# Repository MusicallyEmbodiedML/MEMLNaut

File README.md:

Hardware for the MEMLNaut instrument

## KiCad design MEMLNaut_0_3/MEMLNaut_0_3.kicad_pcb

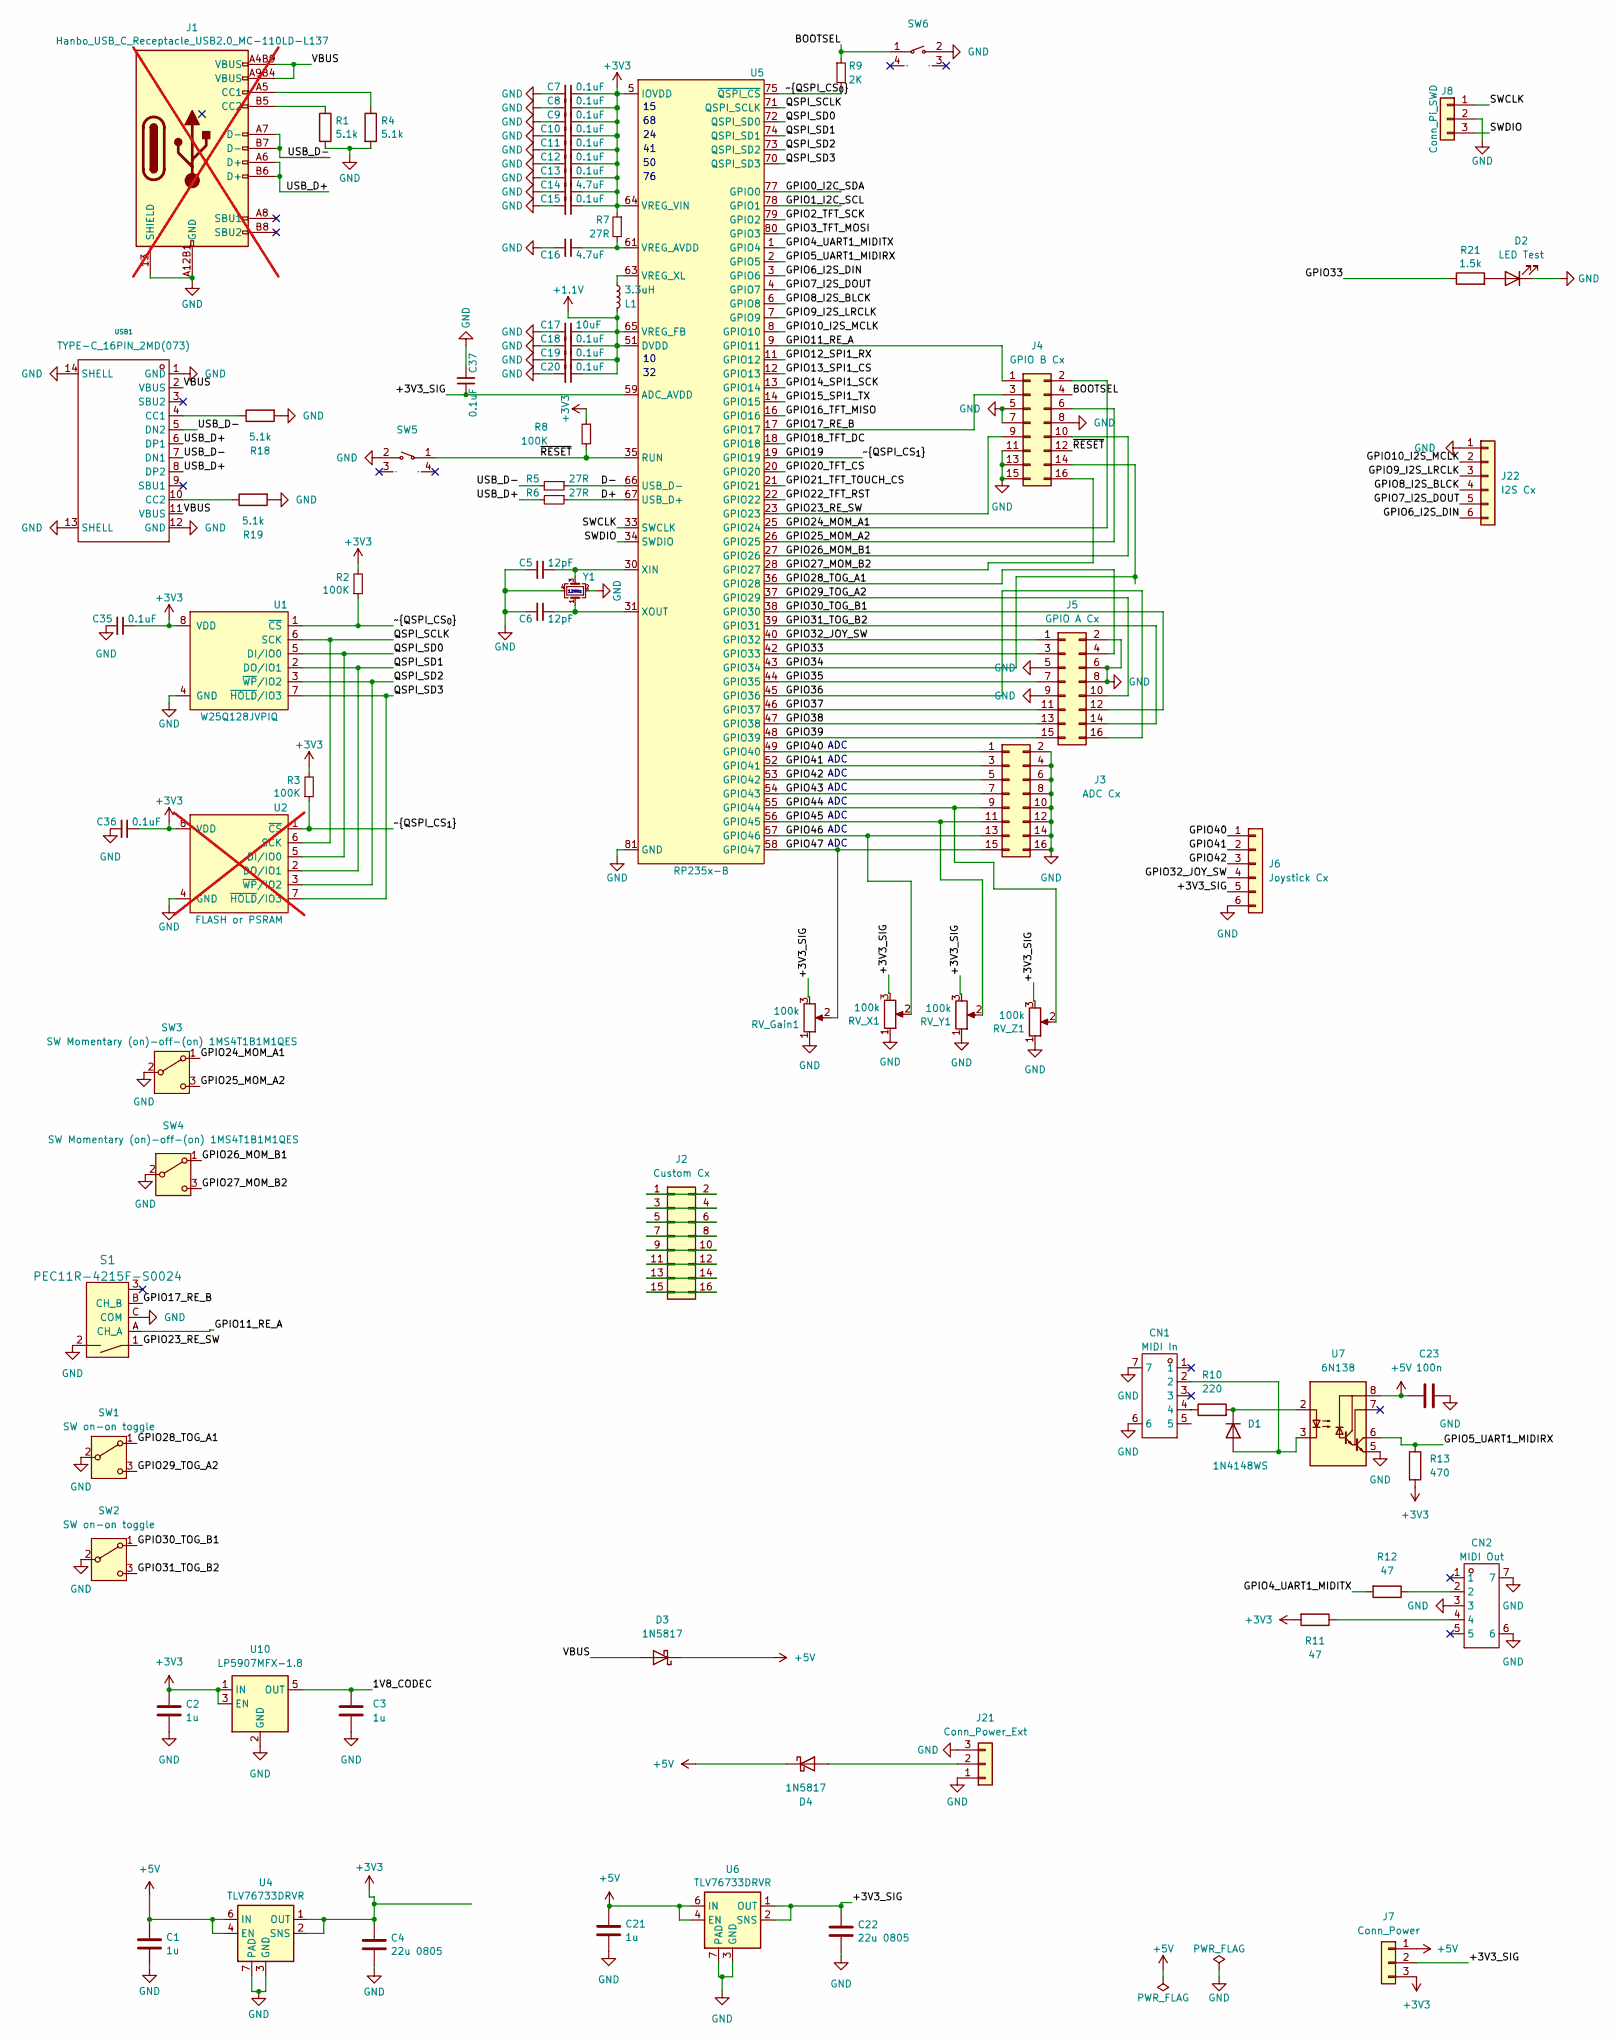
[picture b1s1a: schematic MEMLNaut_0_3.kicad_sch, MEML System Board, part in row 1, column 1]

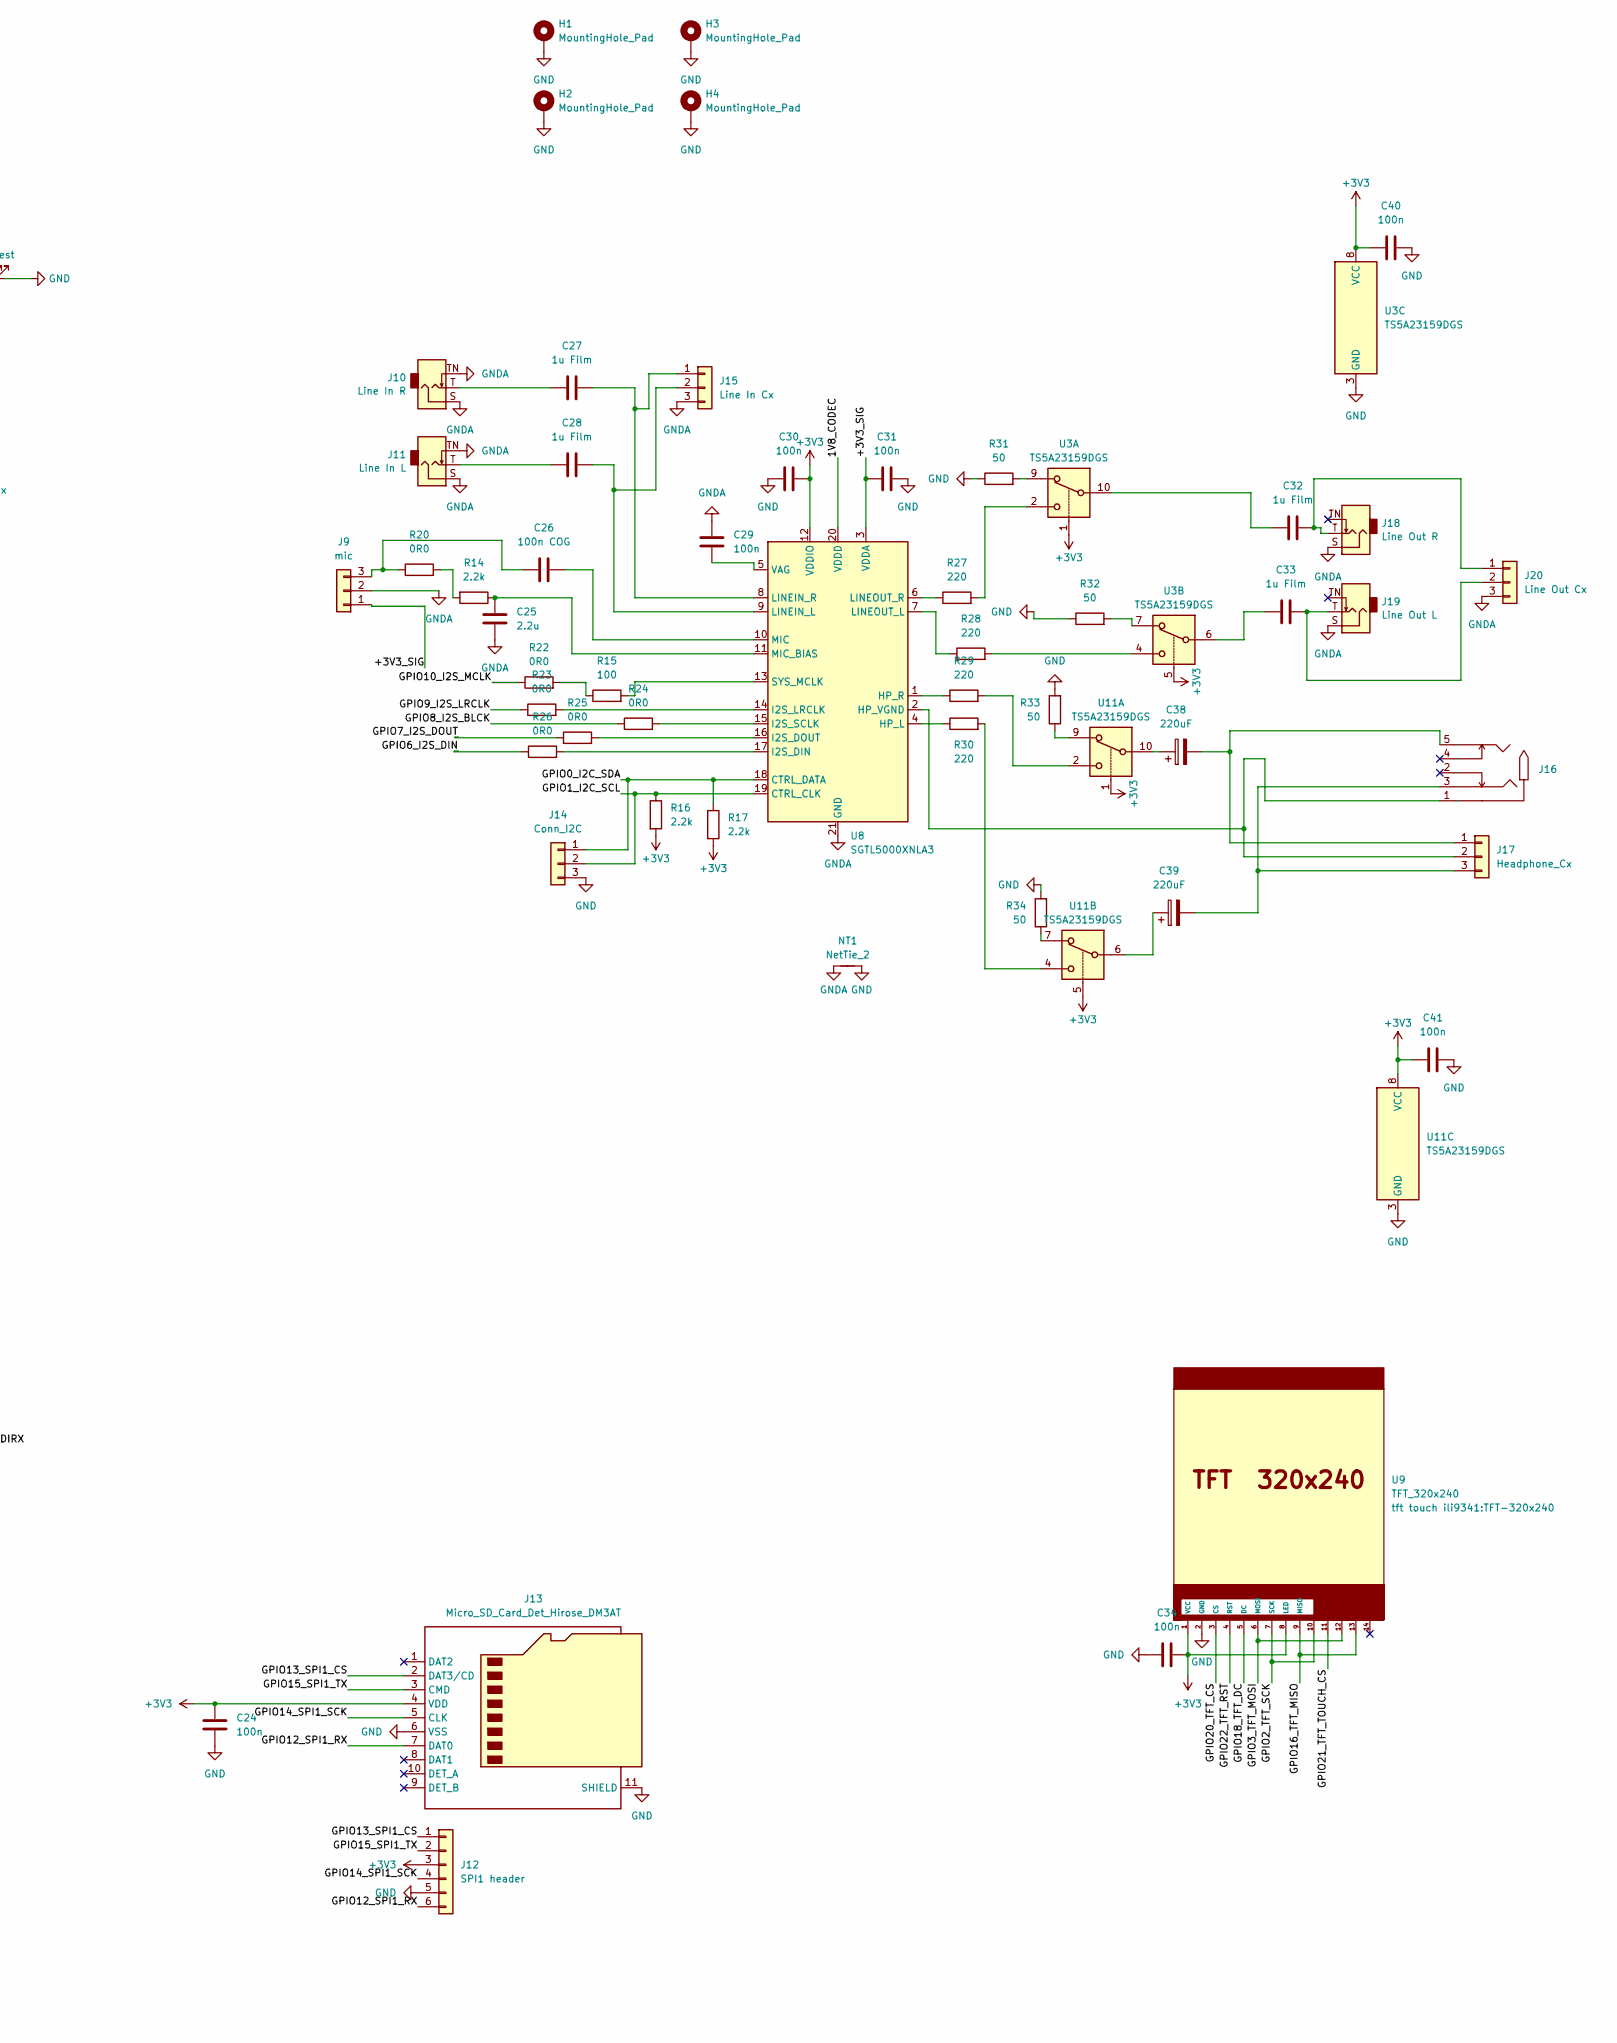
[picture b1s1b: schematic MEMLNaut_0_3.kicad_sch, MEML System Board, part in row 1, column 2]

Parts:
C1, C2, C21: 1u; C_0603_1608Metric_Pad1.08x0.95mm_HandSolder
C3: 1u; C_0603_1608Metric
C4, C22: 22u 0805; C_0805_2012Metric_Pad1.18x1.45mm_HandSolder
C5, C6: 12pF; C_0603_1608Metric
C7, C8, C9, C10, C11, C12, C13, C15, C18, C19, C20, C35, C36, C37: 0.1uF; C_0603_1608Metric
C14, C16: 4.7uF; C_0603_1608Metric
C17: 10uF; C_0603_1608Metric
C23, C24, C29, C30, C31, C34, C40, C41: 100n; C_0603_1608Metric
C25: 2.2u; C_0603_1608Metric
C26: 100n COG; C_Rect_L13.0mm_W5.0mm_P10.00mm_FKS3_FKP3_MKS4; JLC C109501
C27, C28, C32, C33: 1u Film; C_Rect_L13.0mm_W6.0mm_P10.00mm_FKS3_FKP3_MKS4; JLC C2928853
C38, C39: 220uF; CP_Elec_8x10; JLC C445468
CN1: MIDI In; CONN-TH_DIN-504B-M10; Manufacturer Part DIN-504B-M10; LCSC Part Name DIN-504B-M10
CN2: MIDI Out; CONN-TH_DIN-504B-M10; Manufacturer Part DIN-504B-M10; LCSC Part Name DIN-504B-M10
D1: 1N4148WS; D_SOD-323
D2: LED Test; LED_0805_2012Metric
D3, D4: 1N5817; D_SOD-323
H1, H2, H3, H4: MountingHole_Pad; MountingHole_2.2mm_M2_DIN965_Pad
J1: Hanbo_USB_C_Receptacle_USB2.0_MC-110LD-L137; USB-C-TH_MC-110LD-L137-A; not fitted
J2: Custom Cx; HDR-SMD_16P-P2.54-V-M-R2-C8-S7.4; JLC C3294466
J3: ADC Cx; HDR-SMD_16P-P2.54-V-M-R2-C8-S7.4; JLC C3294466
J4: GPIO B Cx; HDR-SMD_16P-P2.54-V-M-R2-C8-S7.4; JLC C3294466
J5: GPIO A Cx; HDR-SMD_16P-P2.54-V-M-R2-C8-S7.4; JLC C3294466
J6: Joystick Cx; HDR-SMD_6P-P2.54-V-M-S4.8; JLC C5160789
J7: Conn_Power; HDR-TH_3P-P2.54_DZ254S-11-03-48; JLC C5160786
J8: Conn_Pi_SWD; HDR-TH_3P-P2.54_DZ254S-11-03-48; JLC C5160786
J9: mic; HDR-TH_3P-P2.54_DZ254S-11-03-48; JLC C5160786
J10: Line In R; Jack_3.5mm_QingPu_WQP-PJ398SM_Vertical_CircularHoles
J11: Line In L; Jack_3.5mm_QingPu_WQP-PJ398SM_Vertical_CircularHoles
J12: SPI1 header; PinHeader_1x06_P2.54mm_Vertical; JLC C5160789
J13: Micro_SD_Card_Det_Hirose_DM3AT; microSD_HC_Hirose_DM3AT-SF-PEJM5; JLC C114218
J14: Conn_I2C; HDR-TH_3P-P2.54_DZ254S-11-03-48; JLC C5160786
J15: Line In Cx; HDR-TH_3P-P2.54_DZ254S-11-03-48; JLC C5160786
J16: AUDIO-TH_PJ-325C; Manufacturer Part PJ325外铜套; LCSC Part Name 3.5mm耳机座
J17: Headphone_Cx; HDR-TH_3P-P2.54_DZ254S-11-03-48; JLC C5160786
J18: Line Out R; Jack_3.5mm_QingPu_WQP-PJ398SM_Vertical_CircularHoles
J19: Line Out L; Jack_3.5mm_QingPu_WQP-PJ398SM_Vertical_CircularHoles
J20: Line Out Cx; HDR-TH_3P-P2.54_DZ254S-11-03-48; JLC C5160786
J21: Conn_Power_Ext; HDR-TH_3P-P2.54_DZ254S-11-03-48; JLC C5160786
J22: I2S Cx; HDR-SMD_6P-P2.54-V-M-S4.8; JLC C5160789
L1: 3.3uH; IND-SMD_L2.0-W1.6_AOTA-B201610S3R3-101-T; JLC C42411119
NT1: NetTie_2; NetTie-2_SMD_Pad0.5mm
R1, R4, R18, R19: 5.1k; R_0402_1005Metric
R2, R3, R8: 100K; R_0603_1608Metric
R5, R6, R7: 27R; R_0603_1608Metric
R9: 2K; R_0603_1608Metric
R10, R27, R28, R29, R30: 220; R_0603_1608Metric
R11, R12: 47; R_0603_1608Metric
R13: 470; R_0603_1608Metric
R14, R16, R17: 2.2k; R_0603_1608Metric
R15: 100; R_0603_1608Metric
R20, R22, R23, R24, R25, R26: 0R0; R_0603_1608Metric
R21: 1.5k; R_0603_1608Metric
R31, R32, R33, R34: 50; R_0603_1608Metric
RV_Gain1: 100k; Alpha9mmPot
RV_X1: 100k; Alpha9mmPot
RV_Y1: 100k; Alpha9mmPot
RV_Z1: 100k; Alpha9mmPot
S1: PEC11R-4215F-S0024; Rotary_Encoder_Switched_PEC11R; MPN PEC11R-4215F-S0024; Digi-Key_PN PEC11R-4215F-S0024-ND
SW1, SW2: SW on-on toggle; Thonk DWB2
SW3, SW4: SW Momentary (on)-off-(on) 1MS4T1B1M1QES; Thonk DWB2
SW5, SW6: SW-TH_K2-1102AQ-C4CW-01; Manufacturer Part K2-1102AQ-C4CW-01; LCSC Part Name 6*6*5塑头,260G,行程0.25mm,侧脚
U1: W25Q128JVPIQ; WSON-8-1EP_6x5mm_P1.27mm_EP3.4x4mm; LCSC C190862
U2: FLASH or PSRAM; SSOP-8_5.25x5.24mm_P1.27mm; not fitted
U3, U11: TS5A23159DGS; VSSOP-10_3x3mm_P0.5mm
U4, U6: TLV76733DRVR; WSON-6-1EP_2x2mm_P0.65mm_EP1x1.6mm_ThermalVias
U5: RP235x-B; QFN-80_EP_10x10_Pitch0.4mm
U7: 6N138; DIP-8_W7.62mm; JLC C571211
U8: SGTL5000XNLA3; QFN-20-1EP_3x3mm_P0.4mm_EP1.65x1.65mm
U9: TFT_320x240; TFT-320x240
U10: LP5907MFX-1.8; SOT-23-5; JLC C92498
USB1: TYPE-C_16PIN_2MD(073); USB-C-SMD_TYPE-C-6PIN-2MD-073; JLC C2765186
Y1: CM4012M00012001; Crystal_SMD_2520-4Pin_2.5x2.0mm; LCSC C7294611

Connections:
+1.1V: C17.1, C18.1, C19.1, C20.1, L1.2, U5.10 (DVDD), U5.32 (DVDD), U5.51 (DVDD), U5.65 (VREG_FB)
+3V3: C2.1, C4.1, C7.1, C8.1, C9.1, C10.1, C11.1, C12.1, C13.1, C14.1, C15.1, C24.1, C30.2, C34.2, C35.1, C36.1, C40.1, C41.1, J7.3, J12.3, J13.4 (VDD), R2.2, R3.2, R7.1, R8.1, R11.2, R13.2, R16.2, R17.2, U1.8 (VDD), U2.8 (VDD), U3.1, U3.5, U3.8 (VCC), U4.1 (OUT), U4.2 (SNS), U5.5 (IOVDD), U5.15 (IOVDD), U5.24 (IOVDD), U5.29 (IOVDD), U5.41 (IOVDD), U5.50 (IOVDD), U5.60 (IOVDD), U5.64 (VREG_VIN), U5.68 (IOVDD), U5.69 (IOVDD), U5.76 (IOVDD), U8.12 (VDDIO), U9.1 (VCC), U9.8 (LED), U10.1 (IN), U10.3 (EN), U11.1, U11.5, U11.8 (VCC)
+5V: C1.1, C21.1, C23.1, D3.1 (K), D4.1 (K), J7.1, U4.4 (EN), U4.6 (IN), U6.4 (EN), U6.6 (IN), U7.8 (VCC)
/1V8_CODEC: C3.1, U8.20 (VDDD), U10.5 (OUT)
/+3V3_SIG: C22.1, C31.2, C37.1, J6.5, J7.2, J9.1, RV_Gain1.3, RV_X1.3, RV_Y1.3, RV_Z1.3, U5.59 (ADC_AVDD), U6.1 (OUT), U6.2 (SNS), U8.3 (VDDA)
/BOOTSEL: J4.4, R9.1, SW6.1
/D+: R6.1, U5.67 (USB_D+)
/D-: R5.1, U5.66 (USB_D-)
/GPIO0_I2C_SDA: J14.1, R17.1, U5.77 (GPIO0), U8.18 (CTRL_DATA)
/GPIO1_I2C_SCL: J14.2, R16.1, U5.78 (GPIO1), U8.19 (CTRL_CLK)
/GPIO2_TFT_SCK: U5.79 (GPIO2), U9.7 (SCK), U9.10
/GPIO3_TFT_MOSI: U5.80 (GPIO3), U9.6 (MOSI), U9.12
/GPIO4_UART1_MIDITX: R12.2, U5.1 (GPIO4)
/GPIO5_UART1_MIDIRX: R13.1, U5.2 (GPIO5), U7.6 (VO2)
/GPIO6_I2S_DIN: J22.6, R26.1, U5.3 (GPIO6)
/GPIO7_I2S_DOUT: J22.5, R25.1, U5.4 (GPIO7)
/GPIO8_I2S_BLCK: J22.4, R24.1, U5.6 (GPIO8)
/GPIO9_I2S_LRCLK: J22.3, R23.1, U5.7 (GPIO9)
/GPIO10_I2S_MCLK: J22.2, R22.1, U5.8 (GPIO10)
/GPIO11_RE_A: J4.1, S1.A (CH_A), U5.9 (GPIO11)
/GPIO12_SPI1_RX: J12.6, J13.7 (DAT0), U5.11 (GPIO12)
/GPIO13_SPI1_CS: J12.1, J13.2 (DAT3/CD), U5.12 (GPIO13)
/GPIO14_SPI1_SCK: J12.4, J13.5 (CLK), U5.13 (GPIO14)
/GPIO15_SPI1_TX: J12.2, J13.3 (CMD), U5.14 (GPIO15)
/GPIO16_TFT_MISO: U5.16 (GPIO16), U9.9 (MISO), U9.13
/GPIO17_RE_B: J4.3, S1.B (CH_B), U5.17 (GPIO17)
/GPIO18_TFT_DC: U5.18 (GPIO18), U9.5 (DC)
/GPIO19: R3.1, U2.1 (~CS), U5.19 (GPIO19)
/GPIO20_TFT_CS: U5.20 (GPIO20), U9.3 (CS)
/GPIO21_TFT_TOUCH_CS: U5.21 (GPIO21), U9.11
/GPIO22_TFT_RST: U5.22 (GPIO22), U9.4 (RST)
/GPIO23_RE_SW: J4.9, S1.1, U5.23 (GPIO23)
/GPIO24_MOM_A1: J4.2, SW3.1 (A), U5.25 (GPIO24)
/GPIO25_MOM_A2: J4.6, SW3.3 (C), U5.26 (GPIO25)
/GPIO26_MOM_B1: J4.10, SW4.1 (A), U5.27 (GPIO26)
/GPIO27_MOM_B2: J4.16, SW4.3 (C), U5.28 (GPIO27)
/GPIO28_TOG_A1: J5.4, SW1.1 (A), U5.36 (GPIO28)
/GPIO29_TOG_A2: J5.10, SW1.3 (C), U5.37 (GPIO29)
/GPIO30_TOG_B1: J5.12, SW2.1 (A), U5.38 (GPIO30)
/GPIO31_TOG_B2: J5.14, SW2.3 (C), U5.39 (GPIO31)
/GPIO32_JOY_SW: J5.1, J6.4, U5.40 (GPIO32)
/GPIO33: J5.3, R21.1, U5.42 (GPIO33)
/GPIO34: J4.14, U5.43 (GPIO34)
/GPIO35: J5.7, U5.44 (GPIO35)
/GPIO36: J5.16, U5.45 (GPIO36)
/GPIO37: J5.11, U5.46 (GPIO37)
/GPIO38: J5.13, U5.47 (GPIO38)
/GPIO39: J5.15, U5.48 (GPIO39)
/GPIO40: J3.1, J6.1, U5.49 (GPIO40)
/GPIO41: J3.3, J6.2, U5.52 (GPIO41)
/GPIO42: J3.5, J6.3, U5.53 (GPIO42)
/GPIO43: J3.7, U5.54 (GPIO43)
/GPIO44: J3.9, RV_Z1.2, U5.55 (GPIO44)
/GPIO45: J3.11, RV_Y1.2, U5.56 (GPIO45)
/GPIO46: J3.13, RV_X1.2, U5.57 (GPIO46)
/GPIO47: J3.15, RV_Gain1.2, U5.58 (GPIO47)
/QSPI_SCLK: U1.6 (SCK), U2.6 (SCK), U5.71 (QSPI_SCLK)
/QSPI_SD0: U1.5 (DI/IO0), U2.5 (DI/IO0), U5.72 (QSPI_SD0)
/QSPI_SD1: U1.2 (DO/IO1), U2.2 (DO/IO1), U5.74 (QSPI_SD1)
/QSPI_SD2: U1.3 (~WP/IO2), U2.3 (~WP/IO2), U5.73 (QSPI_SD2)
/QSPI_SD3: U1.7 (~HOLD/IO3), U2.7 (~HOLD/IO3), U5.70 (QSPI_SD3)
/SWCLK: J8.1, U5.33 (SWCLK)
/SWDIO: J8.3, U5.34 (SWDIO)
/USB_D+: J1.A6 (D+), J1.B6 (D+), R6.2, USB1.6 (DP1), USB1.8 (DP2)
/USB_D-: J1.A7 (D-), J1.B7 (D-), R5.2, USB1.5 (DN2), USB1.7 (DN1)
/VBUS: D3.2 (A), J1.A4B9 (VBUS), J1.A9B4 (VBUS), USB1.2 (VBUS), USB1.11 (VBUS)
/~QSPI_CS_{0}: R2.1, R9.2, U1.1 (~CS), U5.75 (~QSPI_CS)
/~RESET: J4.12, R8.2, SW5.1, U5.35 (RUN)
GND: C1.2, C2.2, C3.2, C4.2, C5.2, C6.2, C7.2, C8.2, C9.2, C10.2, C11.2, C12.2, C13.2, C14.2, C15.2, C16.2, C17.2, C18.2, C19.2, C20.2, C21.2, C22.2, C23.2, C24.2, C30.1, C31.1, C34.1, C35.2, C36.2, C37.2, C40.2, C41.2, CN1.6, CN1.7, CN2.3, CN2.6, CN2.7, D2.1 (K), H1.1, H2.1, H3.1, H4.1, J1.13 (SHIELD), J1.A1B12 (GND), J1.A12B1 (GND), J3.2, J3.4, J3.6, J3.8, J3.10, J3.12, J3.14, J3.16, J4.5, J4.7, J4.8, J4.11, J4.13, J4.15, J5.2, J5.5, J5.6, J5.8, J5.9, J6.6, J8.2, J12.5, J13.6 (VSS), J13.11 (SHIELD), J14.3, J21.1, J21.3, J22.1, NT1.2, R1.2, R4.2, R18.2, R19.2, R31.1, R32.1, R33.2, R34.2, RV_Gain1.1, RV_X1.1, RV_Y1.1, RV_Z1.1, S1.2, S1.C (COM), SW1.2 (B), SW2.2 (B), SW3.2 (B), SW4.2 (B), SW5.2, SW6.2, U1.4 (GND), U1.9 (GND), U2.4 (GND), U3.3 (GND), U4.3 (GND), U4.5 (GND), U4.7 (PAD), U5.62 (GND), U5.81 (GND), U6.3 (GND), U6.5 (GND), U6.7 (PAD), U7.5 (GND), U9.2 (GND), U10.2 (GND), U11.3 (GND), USB1.1 (GND), USB1.12 (GND), USB1.13 (SHELL), USB1.14 (SHELL), Y1.2, Y1.4
GNDA: C25.2, C29.1, J9.2, J10.S, J10.TN, J11.S, J11.TN, J15.3, J18.S, J19.S, J20.3, NT1.1, U8.21 (GND)
unnamed: C27.2, J10.T
unnamed: C28.1, J11.T
unnamed: C32.1, U3.10
unnamed: C33.1, U3.6
unnamed: C38.1, U11.10
unnamed: C39.1, U11.6
unnamed: CN1.4, R10.1
unnamed: CN2.2, R12.1
unnamed: CN2.4, R11.1
unnamed: CN1.2, D1.2 (A), U7.3 (C2)
unnamed: D1.1 (K), R10.2, U7.2 (C1)
unnamed: D2.2 (A), R21.2
unnamed: D4.2 (A), J21.2
unnamed: J1.A5 (CC1), R4.1
unnamed: J1.B5 (CC2), R1.1
unnamed: J2.1, J2.2
unnamed: J2.3, J2.4
unnamed: J2.5, J2.6
unnamed: J2.7, J2.8
unnamed: J2.9, J2.10
unnamed: J2.11, J2.12
unnamed: J2.13, J2.14
unnamed: J2.15, J2.16
unnamed: C26.1, J9.3, R20.1
unnamed: C27.1, J15.1, U8.8 (LINEIN_R)
unnamed: C28.2, J15.2, U8.9 (LINEIN_L)
unnamed: C38.2, J16.5, J17.1
unnamed: J16.1, J17.2, U8.2 (HP_VGND)
unnamed: C39.2, J16.3, J17.3
unnamed: C32.2, J18.T, J20.1
unnamed: C33.2, J19.T, J20.2
unnamed: R14.2, R20.2
unnamed: R15.1, R22.2
unnamed: R27.2, U3.2
unnamed: R28.2, U3.4
unnamed: R29.2, U11.2
unnamed: R30.2, U11.4
unnamed: R31.2, U3.9
unnamed: R32.2, U3.7
unnamed: R33.1, U11.9
unnamed: R34.1, U11.7
unnamed: C16.1, R7.2, U5.61 (VREG_AVDD)
unnamed: L1.1, U5.63 (VREG_XL)
unnamed: C5.1, U5.30 (XIN), Y1.3
unnamed: C6.1, U5.31 (XOUT), Y1.1
unnamed: R30.1, U8.4 (HP_L)
unnamed: R29.1, U8.1 (HP_R)
unnamed: R26.2, U8.17 (I2S_DIN)
unnamed: R25.2, U8.16 (I2S_DOUT)
unnamed: R23.2, U8.14 (I2S_LRCLK)
unnamed: R24.2, U8.15 (I2S_SCLK)
unnamed: R28.1, U8.7 (LINEOUT_L)
unnamed: R27.1, U8.6 (LINEOUT_R)
unnamed: C26.2, U8.10 (MIC)
unnamed: C25.1, R14.1, U8.11 (MIC_BIAS)
unnamed: R15.2, U8.13 (SYS_MCLK)
unnamed: C29.2, U8.5 (VAG)
unnamed: R18.1, USB1.4 (CC1)
unnamed: R19.1, USB1.10 (CC2)

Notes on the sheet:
ADC
12MHz

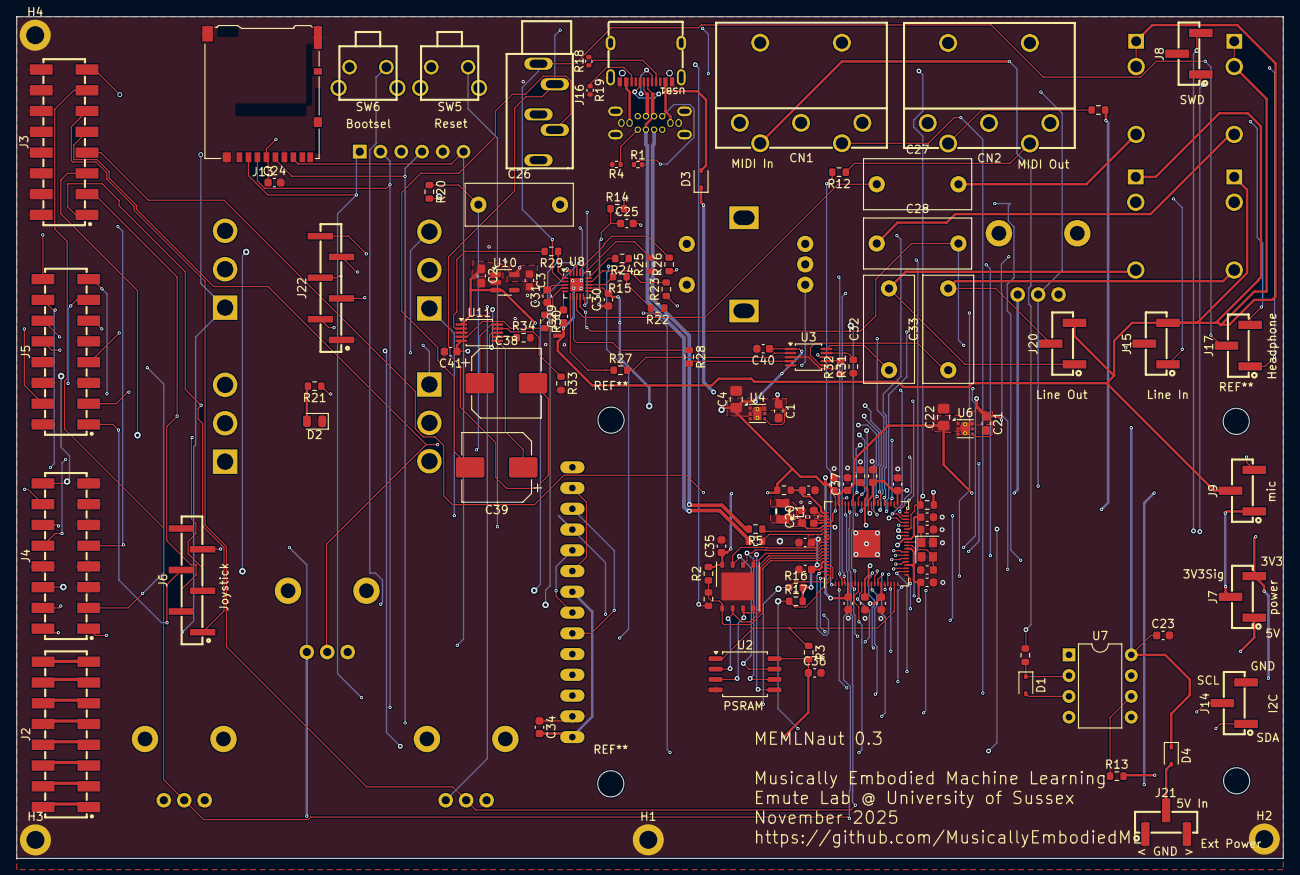
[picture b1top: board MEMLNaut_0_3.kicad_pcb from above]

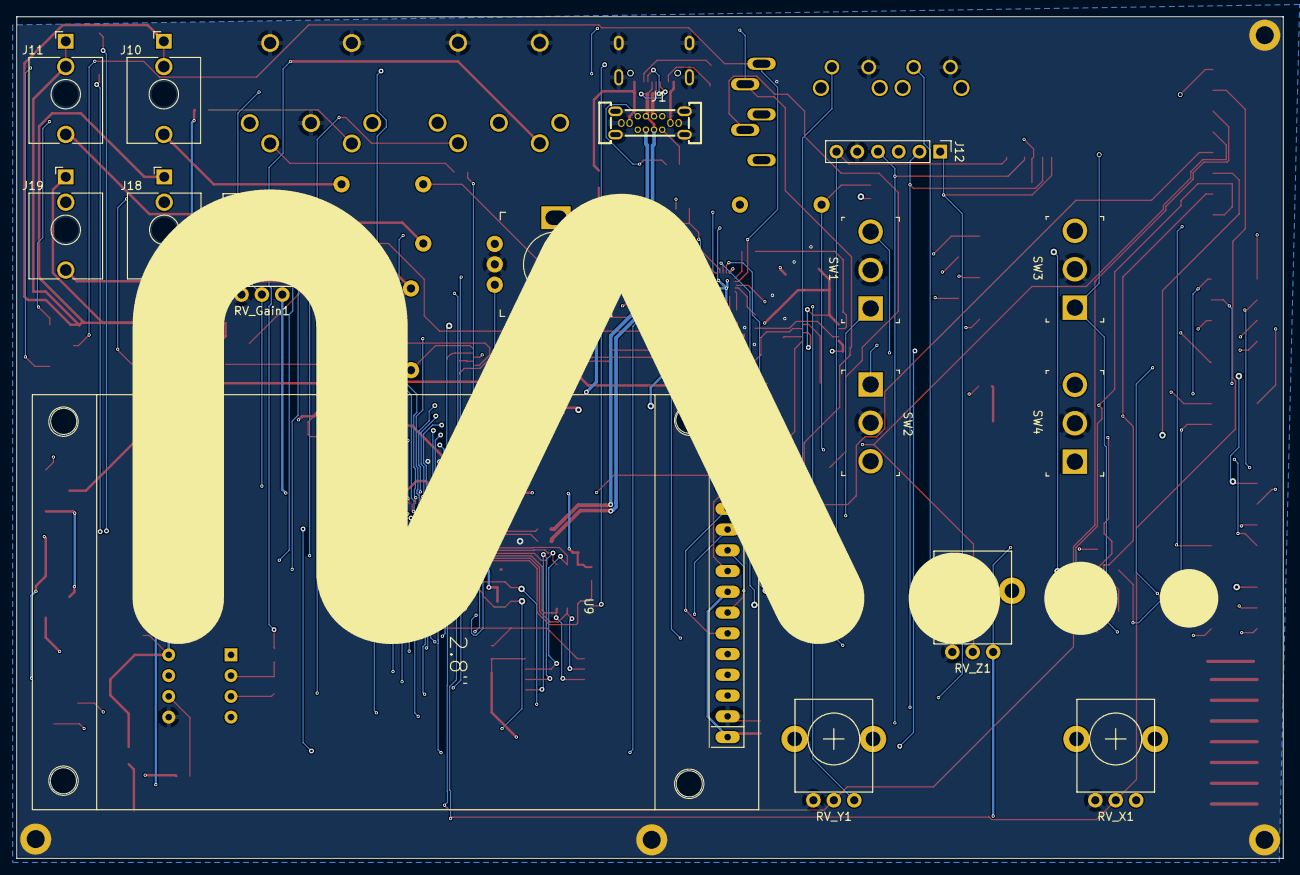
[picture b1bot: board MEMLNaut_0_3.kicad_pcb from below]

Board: 4 copper layers, 155.0 x 103.0 mm, 134 parts (17 on the bottom side), 129 nets.

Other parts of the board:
kibuzzard-6695C28C: G***; kibuzzard-6695C28C

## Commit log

2025-04-08 innit
2025-10-29 Add hardware information for MEMLNaut instrument
2025-11-13 v0.3a
